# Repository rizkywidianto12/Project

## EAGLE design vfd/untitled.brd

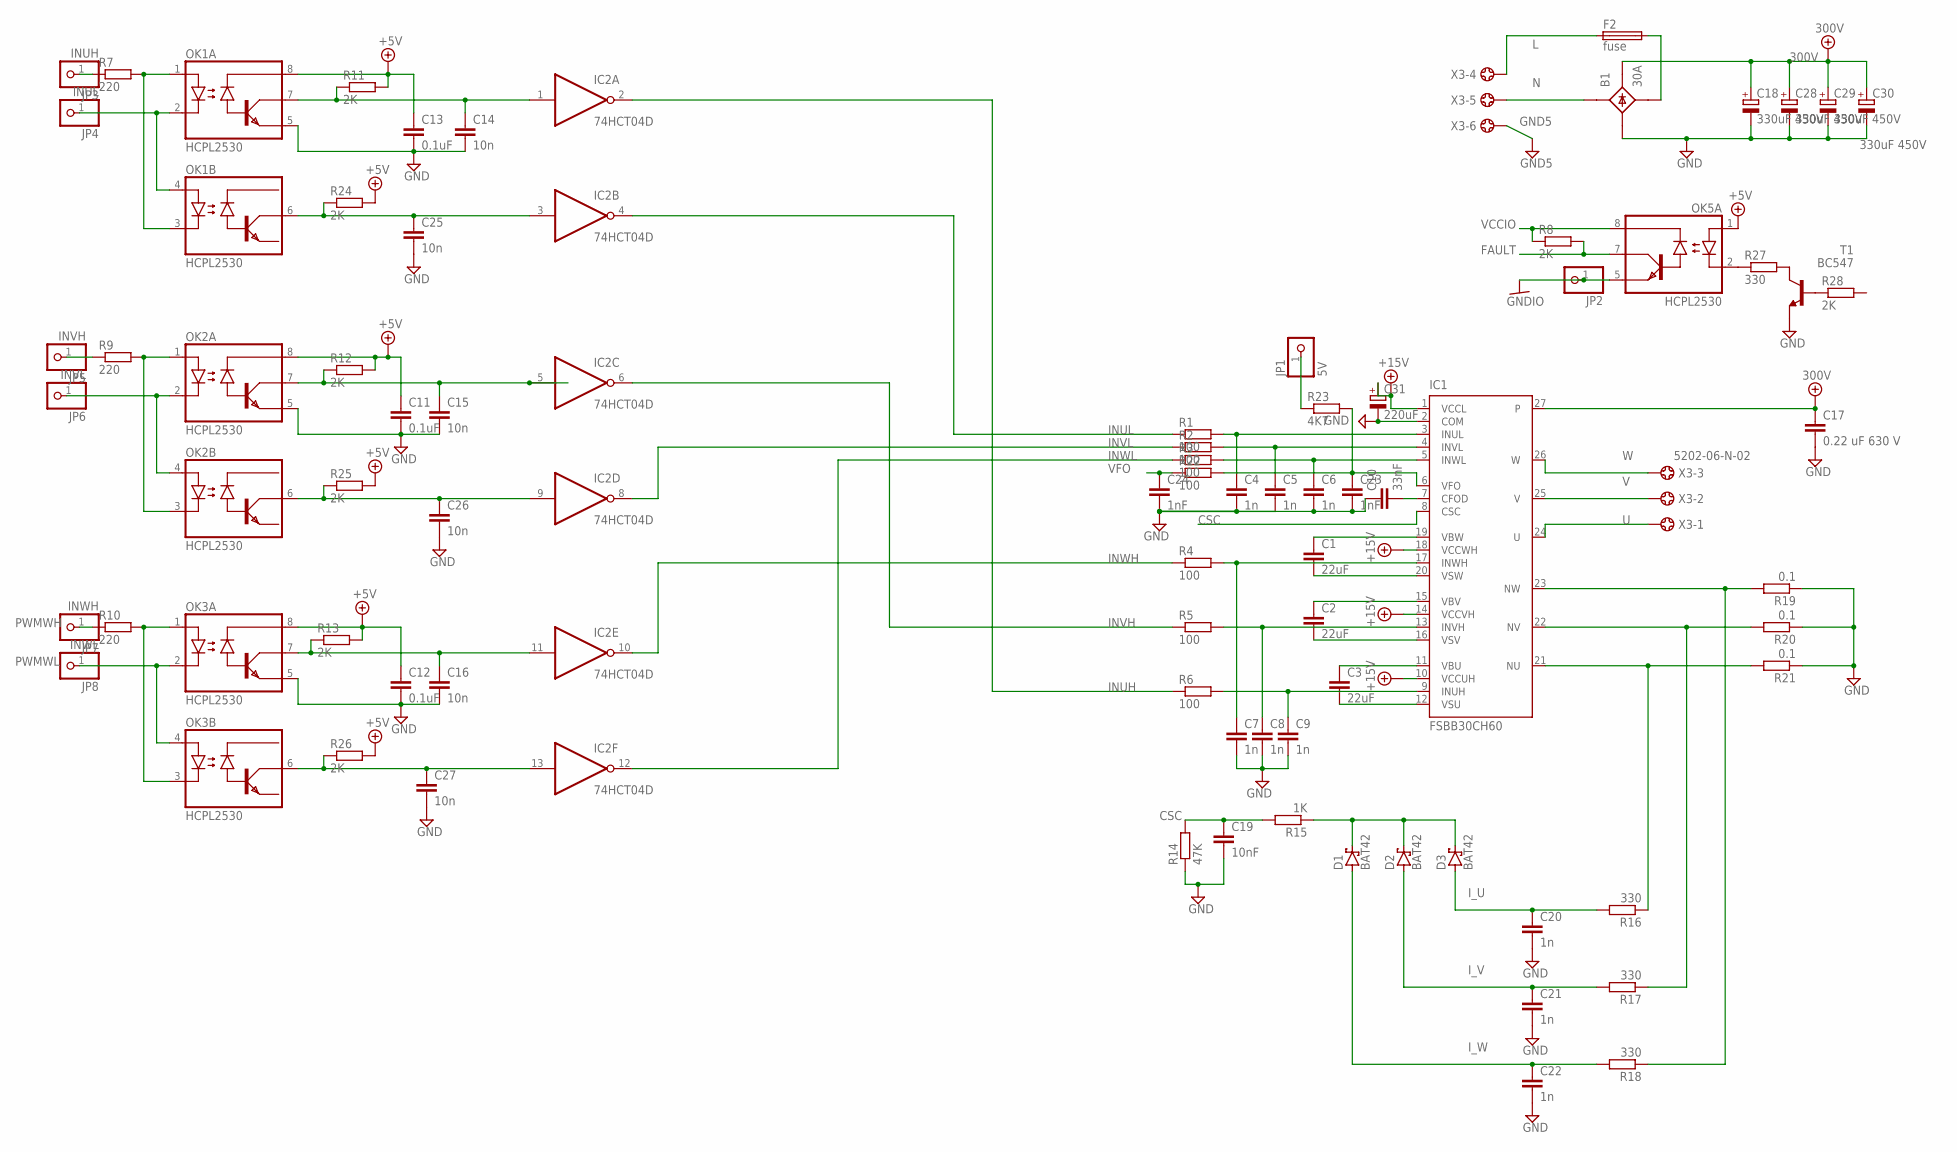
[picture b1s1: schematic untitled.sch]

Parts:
B1: 30A; B25A-
C1, C2, C3: 22uF; C025-024X044
C4, C5, C6, C7, C8, C9, C20, C21, C22: 1n; C025-024X044
C10: 33nF; C025-024X044
C11, C12, C13: 0.1uF; C050-025X075
C14, C15, C16, C25, C26, C27: 10n; C025-024X044
C17: 0.22 uF 630 V; C150-091X182
C18, C28, C29, C30: 330uF 450V; EB35D
C19: 10nF; C025-024X044
C23, C24: 1nF; C025-024X044
C31: 220uF; B45181B
D1, D2, D3: BAT42; DO35-10
F2: fuse; SH22
IC1: FSBB30CH60
IC2: 74HCT04D; SO14
JP1: 5V; 1X01
JP2: PINHD-1X1; 1X01
JP3: INUH; 1X01
JP4: INUL; 1X01
JP5: INVH; 1X01
JP6: INVL; 1X01
JP7: INWH; 1X01
JP8: INWL; 1X01
OK1, OK2, OK3, OK5: HCPL2530; DIL08
R1, R2, R3, R4, R5, R6, R22: 100; 0204/7
R7, R9, R10: 220; 0204/7
R8, R11, R12, R13, R24, R25, R26, R28: 2K; 0204/7
R14: 47K; 0204/7
R15: 1K; 0204/7
R16, R17, R18, R27: 330; 0204/7
R19, R20, R21: 0.1; 0204/7
R23: 4K7; 0204/7
T1: BC547; TO92
X3: 5202-06-N-02

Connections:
3: C4.1, IC1.3 (INUL), R1.2
4: C5.1, IC1.4 (INVL), R2.2
5: C6.1, IC1.5 (INWL), R3.2
6: C23.1, IC1.6 (VFO), R22.2, R23.2
7: C10.2, IC1.7 (CFOD)
9: C9.1, IC1.9 (INUH), R6.2
11: C3.1, IC1.11 (VBU)
13: C8.1, IC1.13 (INVH), R5.2
15: C2.1, IC1.15 (VBV)
16: C2.2, IC1.16 (VSV)
17: C7.1, IC1.17 (INWH), R4.2
19: C1.1, IC1.19 (VBW)
20: C1.2, IC1.20 (VSW)
300V: B1.+1 (+), C17.1, C18.+, C28.+, C29.+, C30.+, IC1.27
+5V: C11.1, C12.1, C13.1, OK1.8 (VCC), OK2.8 (VCC), OK3.8 (VCC), OK5.1 (A1), R11.2, R12.2, R13.2, R24.2, R25.2, R26.2; also elsewhere on the board
+15V: C31.+, IC1.1 (VCCL), IC1.10 (VCCUH), IC1.14 (VCCVH), IC1.18 (VCCWH), IC2.14 (VCC); also elsewhere on the board
CSC: C19.1, IC1.8 (CSC), R14.2, R15.2
FAULT: OK5.7 (VO1), R8.2
GND: B1.-1 (-), C4.2, C5.2, C6.2, C7.2, C8.2, C9.2, C10.1, C11.2, C12.2, C13.2, C14.2, C15.2, C16.2, C17.2, C18.-, C19.2, C20.2, C21.2, C22.2, C23.2, C24.2, C25.2, C26.2, C27.2, C28.-, C29.-, C30.-, C31.-, IC1.2 (COM), IC2.7 (GND), OK1.5 (GND), OK2.5 (GND), OK3.5 (GND), R14.1, R19.1, R20.1, R21.1, T1.1 (E)
GND5: X3.6
GNDIO: JP2.1, OK5.5 (GND)
INUH: IC2.2 (O), R6.1
INUL: IC2.4 (O), R1.1
INVH: IC2.6 (O), R5.1
INVL: IC2.8 (O), R2.1
INWH: IC2.10 (O), R4.1
INWL: IC2.12 (O), R3.1
I_U: C20.1, D3.A, R16.2
I_V: C21.1, D2.A, R17.2
I_W: C22.1, D1.A, R18.2
L: F2.1, X3.4; also elsewhere on the board
N: B1.AC1- (AC1), X3.5; also elsewhere on the board
unnamed: JP1.1, R23.1
unnamed: OK5.2 (C1), R27.1
unnamed: R28.1, T1.2 (B)
unnamed: B1.AC2- (AC2), F2.2
unnamed: R27.2, T1.3 (C)
unnamed: JP3.1, R7.1
unnamed: JP5.1, R9.1
unnamed: C14.1, IC2.1 (I), OK1.7 (VO1), R11.1
unnamed: OK1.1 (A1), OK1.3 (C2), R7.2
unnamed: JP4.1, OK1.2 (C1), OK1.4 (A2)
unnamed: C15.1, IC2.5 (I), OK2.7 (VO1), R12.1
unnamed: C25.1, IC2.3 (I), OK1.6 (VO2), R24.1
unnamed: D1.C, D2.C, D3.C, R15.1
unnamed: IC1.21 (NU), R16.1, R21.2
unnamed: IC1.22 (NV), R17.1, R20.2
unnamed: IC1.23 (NW), R18.1, R19.2
unnamed: C27.1, IC2.13 (I), OK3.6 (VO2), R26.1
unnamed: C16.1, IC2.11 (I), OK3.7 (VO1), R13.1
unnamed: C26.1, IC2.9 (I), OK2.6 (VO2), R25.1
unnamed: JP6.1, OK2.2 (C1), OK2.4 (A2)
unnamed: OK2.1 (A1), OK2.3 (C2), R9.2
unnamed: OK3.1 (A1), OK3.3 (C2), R10.2
PWMWH: JP7.1, R10.1
PWMWL: JP8.1, OK3.2 (C1), OK3.4 (A2)
U: IC1.24 (U), X3.1
V: IC1.25 (V), X3.2
VCCIO: OK5.8 (VCC), R8.1
VFO: C24.1, R22.1
VSU: C3.2, IC1.12 (VSU)
W: IC1.26 (W), X3.3

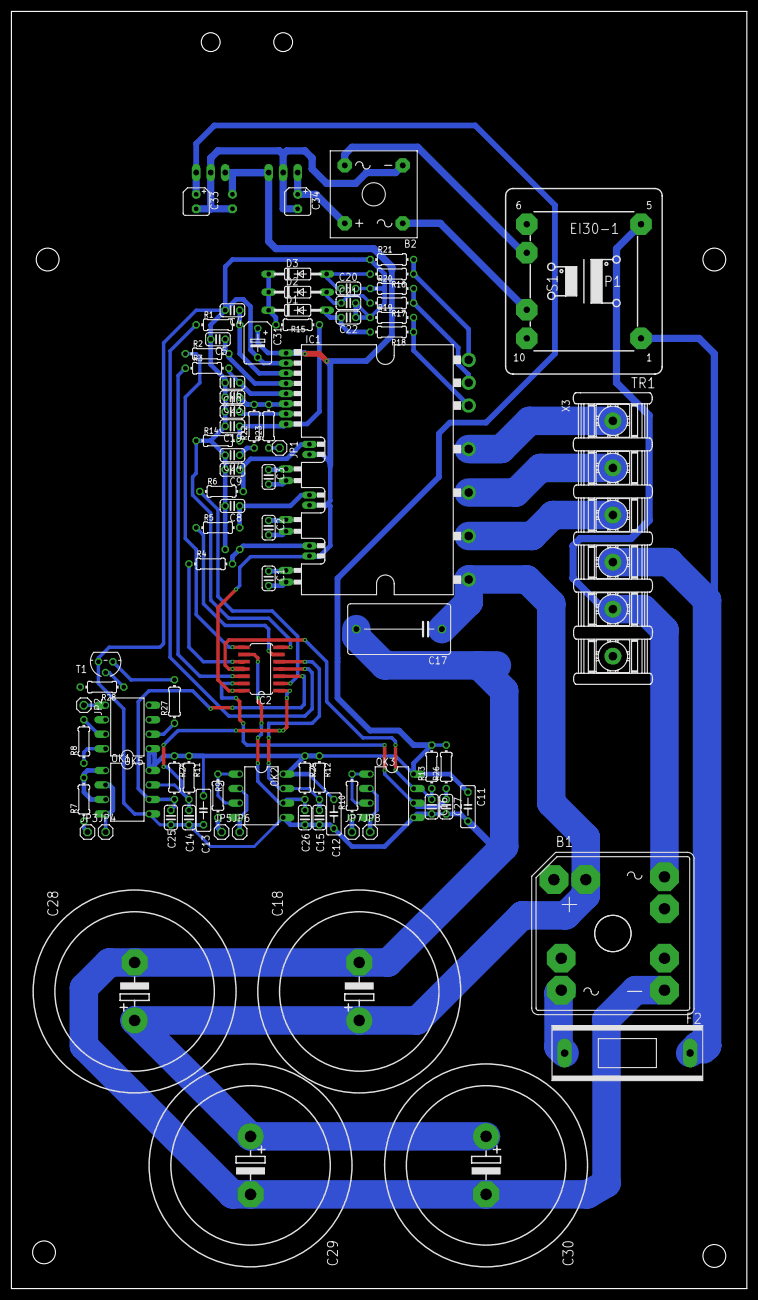
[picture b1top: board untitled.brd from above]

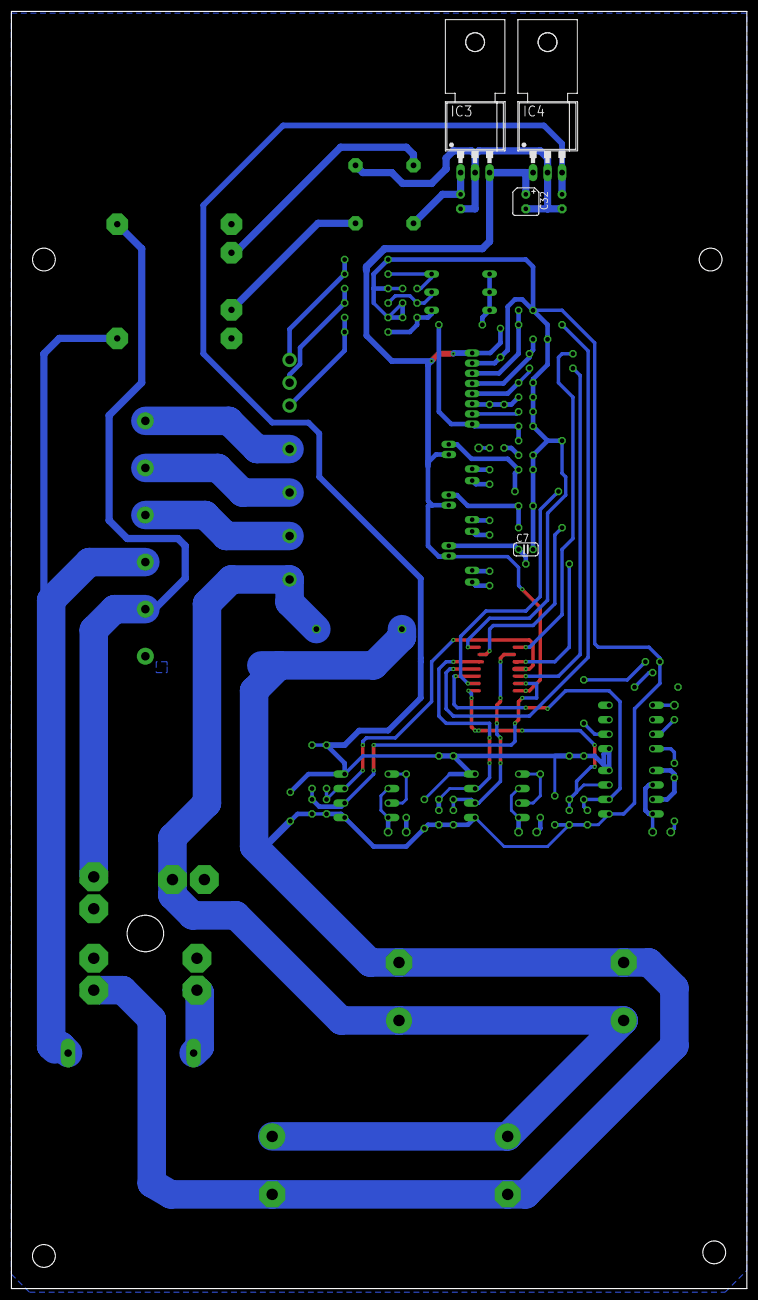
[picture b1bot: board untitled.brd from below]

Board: 2 copper layers, 128.9 x 223.8 mm, 87 parts (4 on the bottom side), 65 nets.

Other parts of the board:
B2: S41
C32, C33, C34: B45181A
IC3: 15; 78MXXL
IC4: 5; 78MXXL
TR1: EI30-1

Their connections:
+5V: C33.+, IC4.OUT; also elsewhere on the board
+15V: C32.+, IC3.OUT, IC4.IN; also elsewhere on the board
L: TR1.1; also elsewhere on the board
N: TR1.5; also elsewhere on the board
unnamed: B2.AC1, TR1.9
unnamed: B2.AC2, TR1.7
unnamed: B2.+, C34.+, IC3.IN
unnamed: B2.-, C32.-, C33.-, C34.-, IC3.GND, IC4.GND

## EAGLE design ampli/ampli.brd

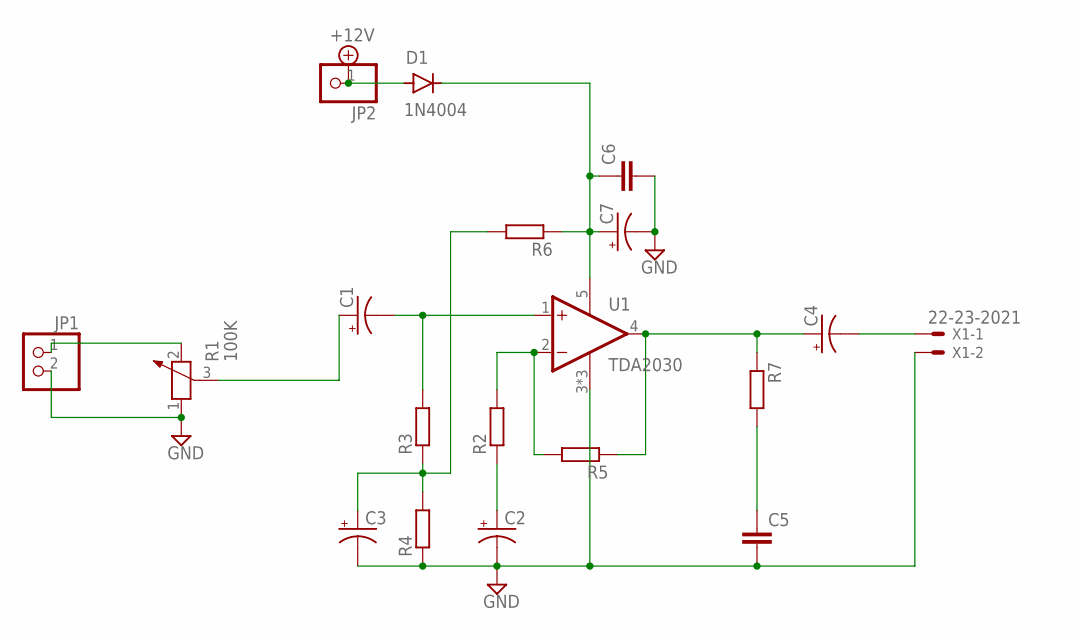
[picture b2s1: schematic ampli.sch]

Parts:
C1, C2, C3: CPOL-USB45181A; B45181A
C4, C7: CPOL-USB45181B; B45181B
C5, C6: C-EU025-024X044; C025-024X044
D1: 1N4004; DO-41
JP1: PINHD-1X2; 1X02
JP2: PINHD-1X1; 1X01
R1: 100K; PT-10
R2, R3, R4, R5, R6, R7: R-EU_0204/5; 0204/5
U1: TDA2030; TO170P1580X1040X480-5
X1: 22-23-2021

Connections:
+12V: D1.A, JP2.1
GND: C2.-, C3.-, C5.2, C6.2, C7.-, JP1.2, R1.1, R4.1, U1.3 (-VS), U1.6 (-VS), U1.6.1 (-VS), X1.2
unnamed: C1.-, R3.2, U1.1 (NON_INV_INPUT)
unnamed: C4.-, X1.1
unnamed: C3.+, R3.1, R4.2, R6.2
unnamed: JP1.1, R1.2
unnamed: R2.2, R5.2, U1.2 (INV_INPUT)
unnamed: C4.+, R5.1, R7.1, U1.4 (OUTPUT)
unnamed: C2.+, R2.1
unnamed: C5.1, R7.2
unnamed: C6.1, C7.+, D1.C, R6.1, U1.5 (+VS)
unnamed: C1.+, R1.3

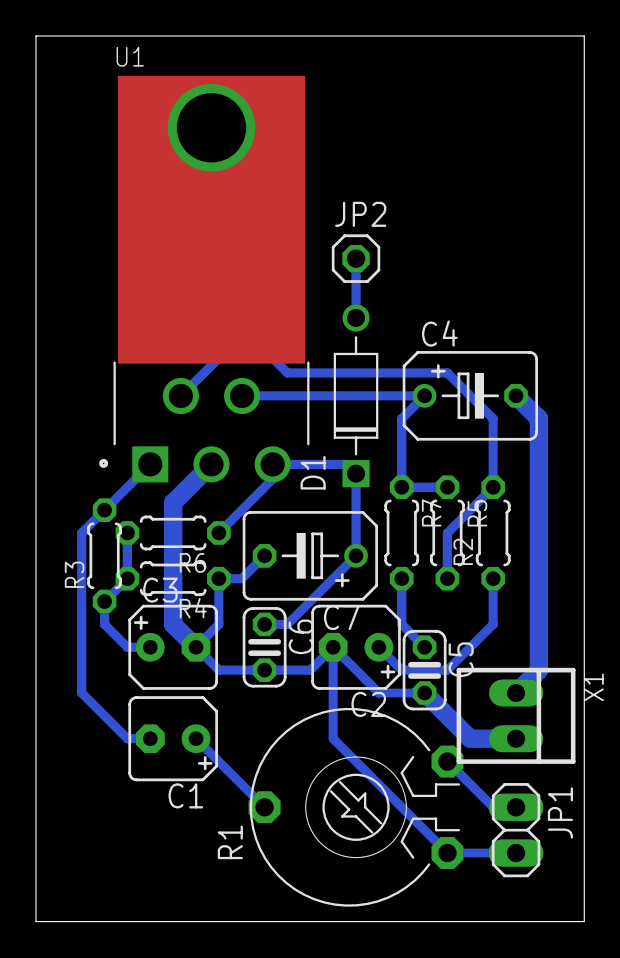
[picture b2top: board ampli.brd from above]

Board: 2 copper layers, 30.5 x 49.2 mm, 19 parts (0 on the bottom side), 12 nets.

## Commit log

2022-03-07 upload
2022-03-07 Update List part
    tambah trafo 15v dan rangkaian rectifier untuk driver
2022-03-08 update trafo
    trafo 15v
2022-03-09 ganti nama
